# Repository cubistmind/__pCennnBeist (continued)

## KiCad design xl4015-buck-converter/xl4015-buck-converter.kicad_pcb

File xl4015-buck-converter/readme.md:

# DC-DC Buck Converter (XL4015)

An adjustable step-down (buck) DC-DC converter PCB built around the XL4015 switching regulator. Designed in KiCad 10.

## Specs

| Parameter | Value |
|---|---|
| Topology | Buck (step-down), non-synchronous |
| Regulator IC | XL4015 |
| Input voltage | Up to 36V DC |
| Output voltage | Adjustable via onboard trim pot |
| Switching frequency | 180 kHz |
| Max output current | 5A (thermal/layout dependent) |
| Board | 2-layer |

## Key components

| Ref | Part | Value |
|---|---|---|
| U1 | XL4015 | Buck regulator, TO-263-5 |
| L1 | Power inductor | 47 µH / 5A |
| D1 | Schottky diode | MBDR1045G (freewheeling/catch diode) |
| CIN1 | Input capacitor | 220 µF / 50V |
| COUT1 | Output capacitor | 470 µF / 35V |
| R1 | Trim potentiometer | 3.3 kΩ (output voltage adjust) |
| R2 | Resistor | 10 kΩ (feedback divider) |
| J1 | Input connector | 2-pin screw terminal |
| J2 | Output connector | 2-pin screw terminal |

## Repo contents

- `xl4015-buck-converter.kicad_pro` — KiCad project file
- `xl4015-buck-converter.kicad_sch` — Schematic
- ` xl4015-buck-converter.kicad_pcb` — PCB layout
- `xl4015-buck-converter.zip` — Gerbers / fabrication files

## Building the board

1. Open `xl4015-buck-converter.kicad_pro` in KiCad 10.
2. Run DRC (**Inspect → Design Rules Checker**) and review any outstanding warnings before ordering.
3. Generate fabrication files: **File → Plot** for Gerbers, then **Generate Drill Files** for the Excellon drill file.
4. Send the Gerber + drill package to your board house (2-layer, standard 1.6mm thickness works with the default footprints).

## Usage

1. Connect your DC input source to J1, respecting polarity.
2. Before connecting a load, power the board and measure the output voltage at J2 with a multimeter.
3. Adjust R1 to set the desired output voltage.
4. Connect your load to J2 once the output is verified.

**Note:** this is a non-isolated converter — input and output share a common ground. Confirm your input voltage stays within the input capacitor and IC ratings before powering it up.

## License

*(Add a license here — e.g. MIT for the design files, or CERN-OHL if you want an open-hardware-specific license.)*

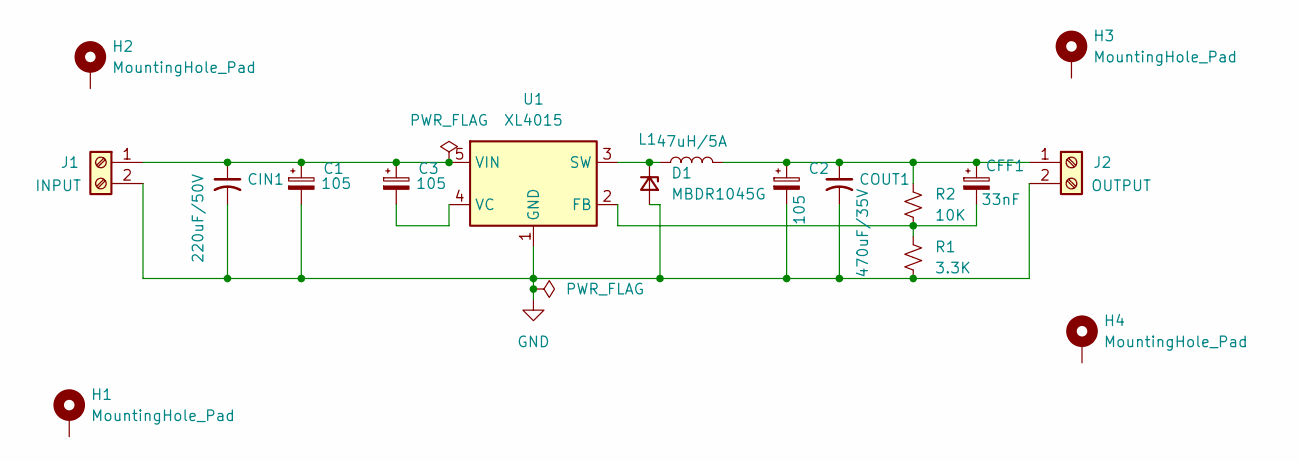
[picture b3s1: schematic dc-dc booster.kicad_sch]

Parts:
C1, C2, C3: 105; C_0805_2012Metric
CFF1: 33nF; C_0805_2012Metric
CIN1: 220uF/50V; CP_Radial_D10.0mm_P5.00mm
COUT1: 470uF/35V; CP_Radial_D10.0mm_P5.00mm
D1: MBDR1045G; TO-252-2
H1, H2, H3, H4: MountingHole_Pad; MountingHole_2.2mm_M2_DIN965_Pad_TopBottom
J1: INPUT; TerminalBlock_MaiXu_MX126-5.0-02P_1x02_P5.00mm
J2: OUTPUT; TerminalBlock_MaiXu_MX126-5.0-02P_1x02_P5.00mm
L1: 47uH/5A; L_12x12mm_H4.5mm
R1: 3.3K; Potentiometer_Bourns_3296W_Vertical
R2: 10K; Potentiometer_Bourns_3296W_Vertical
U1: XL4015; TO-263-5_TabPin3

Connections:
GND: C1.2, C2.2, CIN1.2, COUT1.2, D1.2 (A), J1.2, J2.2, R1.2, U1.1 (GND)
unnamed: D1.1 (K), L1.1, U1.3 (SW)
unnamed: C1.1, C3.1, CIN1.1, J1.1, U1.5 (VIN)
unnamed: C2.1, CFF1.1, COUT1.1, J2.1, L1.2, R2.1
unnamed: CFF1.2, R1.1, R2.2, U1.2 (FB)
unnamed: C3.2, U1.4 (VC)

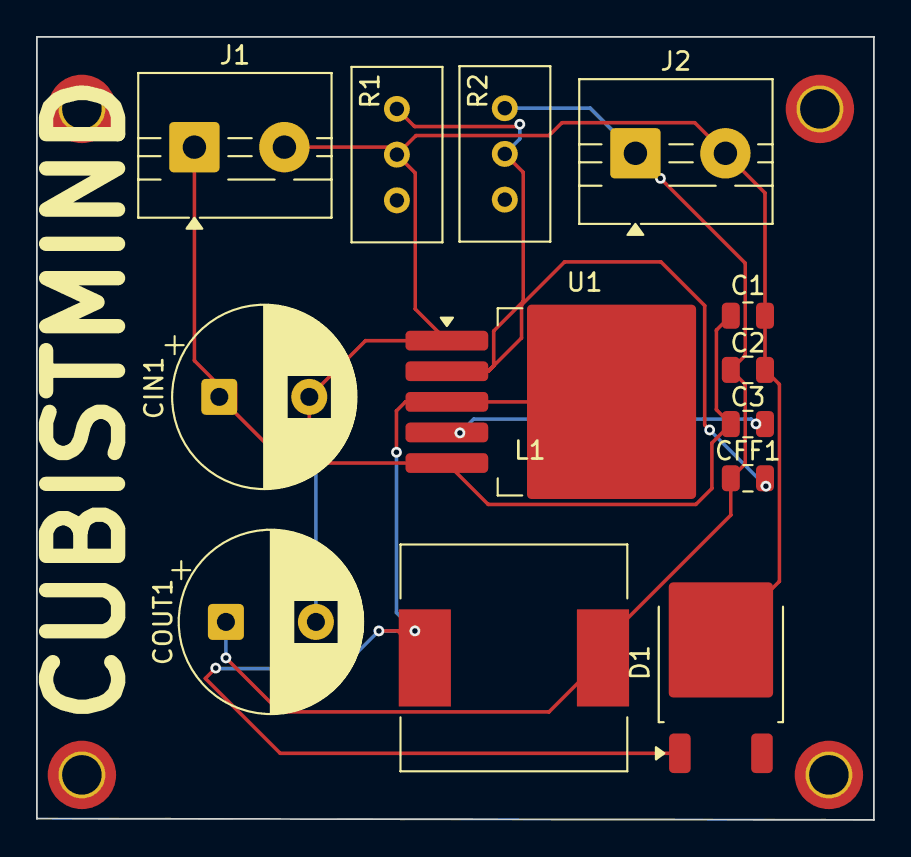
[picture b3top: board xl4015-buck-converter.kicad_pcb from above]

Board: 2 copper layers, 46.5 x 43.5 mm, 17 parts (0 on the bottom side), 6 nets.
